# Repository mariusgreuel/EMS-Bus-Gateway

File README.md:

# EMS Bus Gateway

This repository contains a schematic and PCB layout of an **EMS Bus Gateway**. With the EMS Bus Gateway and the [EMS-ESP32](https://github.com/mariusgreuel/EMS-ESP32) firmware, you can connect EMS Bus devices, such as the **Buderus Logamax** boilers to your home automation system.

## Introduction

The assembled EMS Bus Gateway consists of three essential components:

- A voltage level converter that converts the EMS bus voltage levels to 3.3V TTL levels.
- A micro-controller.
- The EMS-ESP32 firmware.

The schematic uses a modified level convertor from the EMS reference schematic circulating the internet. For the micro-controller, a $5 [Seeed Studio XIAO ESP32C3](https://www.seeedstudio.com/Seeed-XIAO-ESP32C3-p-5431.html) board is used. The micro-controller needs to be programmed with [EMS-ESP32](https://github.com/mariusgreuel/EMS-ESP32) firmware, which is capable of decoding the EMS bus protocol and broadcasting the EMS parameters into your network via MQTT. Finally, the assembled board may be fitted into a **Hammond 1551KGY** enclosure.

The assembled EMS Bus Gateway board looks like this:

## EMS Bus Background

Many Buderus devices, such as the **Buderus Logamax plus GB132 T** boiler, use a bus system called **EMS (Energy Management System)** to communicate with other devices, such as the RC30 room controller. The EMS bus is a simple two-wire serial bus that uses voltage/current modulation to transmit data. With the proper hardware and software, you can transmit many parameters of your boiler into your home automation system.

For instance, you could use [Home Assistant](https://www.home-assistant.io/) to monitor the temperatures of your boiler. Here is a screenshot showing the relevant boiler temperatures during a 10 minutes heating interval:

## Build the EMS-ESP32 firmware

To build the EMS-ESP32 firmware, we use the **PlatformIO** toolchain. Please refer to the [PlatformIO documentation](https://docs.platformio.org/en/latest/) on how to install and use **PlatformIO**. According to the original author of the EMS-ESP32 firmware, your should build the firmware on Linux.

Instead of building the firmware locally, you may download pre-built binaries from my [EMS-ESP32 Releases](https://github.com/mariusgreuel/EMS-ESP32/releases).

To setup the **PlatformIO** toolchain, run the following commands in a Linux bash:

```bash
sudo apt install python3
python3 -m venv ~/.venv/ems-esp32
source ~/.venv/ems-esp32/bin/activate
curl -o- https://raw.githubusercontent.com/nvm-sh/nvm/v0.40.1/install.sh | bash
python -m pip install --upgrade pip
pip install platformio
pip install esptool
nvm install 18
nvm use 18
npm install --global yarn
git clone https://github.com/mariusgreuel/ems-esp32.git -b xiao-3.6.5 ~/repos/ems-esp32
```

To build the EMS-ESP32 firmware for a **XIAO ESP32C3**, run the following command:

```bash
source ~/.venv/ems-esp32/bin/activate
nvm use 18
cd ~/repos/ems-esp32
git clean -xdf
platformio run -e seeed_xiao_esp32c3
```

After the build is completed, you will find the binaries in the `.pio\build\seeed_xiao_esp32c3` or `.pio\build\seeed_xiao_esp32s3` folder.

## Flash the EMS-ESP32 firmware

To flash the EMS-ESP32 firmware on the XIAO ESP32, we use the **esptool.py** from Espressif. Please refer to the [Espressif documentation](https://docs.espressif.com/projects/esptool/en/latest/esp32/esptool/index.html) on how to install and use **esptool.py**.

To flash the EMS-ESP32 firmware on a **XIAO ESP32C3**, run the following command:

```bash
esptool.py --chip esp32c3 --port /dev/ttyUSB0 --baud 460800 --before=default_reset --after=hard_reset write_flash 0x0 bootloader.bin 0x8000 partitions.bin 0x10000 firmware.bin
```

## Configure the EMS-ESP32 software

> Note: The documentation below is a quick-start guide to setup the EMS gateway. For detailed instructions, refer to the original documentation at <https://emsesp.github.io/docs/>.

After you have flashed the XIAO ESP32, your need to configure the EMS-ESP32 software to connect it to your local WiFi network. Essentially, the EMS-ESP32 software creates a local WiFi access point that you can connect to. Then, you can open the dashboard of the EMS-ESP32 software using a web browser via a pre-defined username and password and connect the XIAO ESP32 to your local WiFi network:

- Connect the WSP to a USB-C power supply.
- Connect to the new WiFi access point **ems-esp** using the WPA password **ems-esp-neo**.
- Open the URL <http://ems-esp.local/> in a web browser.
- Enter the username **admin** and the password **admin**.

I recommend making the following configuration changes:

- Under **Settings**, set **Board profile** to **Seeed Studio XIAO ESP32C3**.
- Under **Network/Network Settings**, enter the SSID and password of your local WiFi network.
- Under **Access Point/Access Point Settings**, set **Enable Access Point** to **Never**. Before you disable the access point ensure that your EMS Bus gateway has successfully connected to your local WiFi network.
- Under **NTP/NTP Settings**, check **Enable NTP**.
- Under **MQTT/MQTT Settings**, enable MQTT, enter the IP address of your MQTT broker, and enter your MQTT broker credentials. If you run Home Assistant, check **Enable MQTT Discovery**, and set **Discovery Type** to **Home Assistant**.
- Under **Security**, create a new admin user and remove the pre-defined accounts.

As the EMS Bus Gateway is capable of manipulating the settings of your boiler and issuing arbitrary commands, I recommend putting the EMS gateway into **read-only mode**.

> WARNING: If you choose to not enable **read-only mode**, be advised that it is possible to issue powerful commands such starting up the heater of your boiler, which may potentially damage your boiler.

- Under **Settings**, check **Enable read-only mode**.

## Connect the EMS Bus Gateway to your boiler

To connect the EMS Bus Gateway to your boiler, first connect a USB power supply to the USB-C port of the XIAO ESP32. The XIAO ESP32 requires a power supply of 5V. Refer to the [XIAO ESP32C3 documentation](https://wiki.seeedstudio.com/XIAO_ESP32C3_Getting_Started/) for details.

To connect the gateway to the boiler, you can use a 3.5mm TRS audio cable to connect the connector of the EMS Bus Gateway to the service port of your boiler.

The pinout of the TRS service port connector and the EMS Bus Gateway connector is as follows:

Here is a picture of a Buderus Logamax plus GB132T Boiler with a RC30 controller.

Instead of using the service port connector, you can connect a cable directly to the EMS front panel connector of your boiler. In this picture, the left orange/brown connector named **RC** (room controller) may be used. Refer to your boilers service manual for details. The polarity of this connector does not matter.

## Other documents in this repository

- [EMS Bus Gateway Rendering](./docs/ems-bus-gateway-rendering.jpg)
- [EMS Bus Gateway Schematic (PDF))](./docs/ems-bus-gateway-schematic.pdf)
- [EMS Bus Gateway Component Layout (PDF))](./docs/ems-bus-gateway-component-layout.pdf)
- [EMS Bus Gateway Component List (PDF))](./docs/ems-bus-gateway-component-list.pdf)
- [EMS Bus Gateway Gerber Files](./docs/ems-bus-gateway-gerber.zip)
- [EMS Bus Gateway KiCad project](./pcb)

## References

- EMS-ESP Firmware (EMS Bus Gateway Fork): <https://github.com/mariusgreuel/EMS-ESP32>
- EMS-ESP Firmware (Original): <https://github.com/emsesp/EMS-ESP32>
- EMS-ESP Firmware Documentation: <https://emsesp.github.io/docs/>
- Seeed Studio XIAO Documentation: <https://wiki.seeedstudio.com/SeeedStudio_XIAO_Series_Introduction/>

## License

The EMS Bus Gateway schematic, PCB layout, and documentation is released under the GNU GPLv3.

Copyright 2023 Marius Greuel.

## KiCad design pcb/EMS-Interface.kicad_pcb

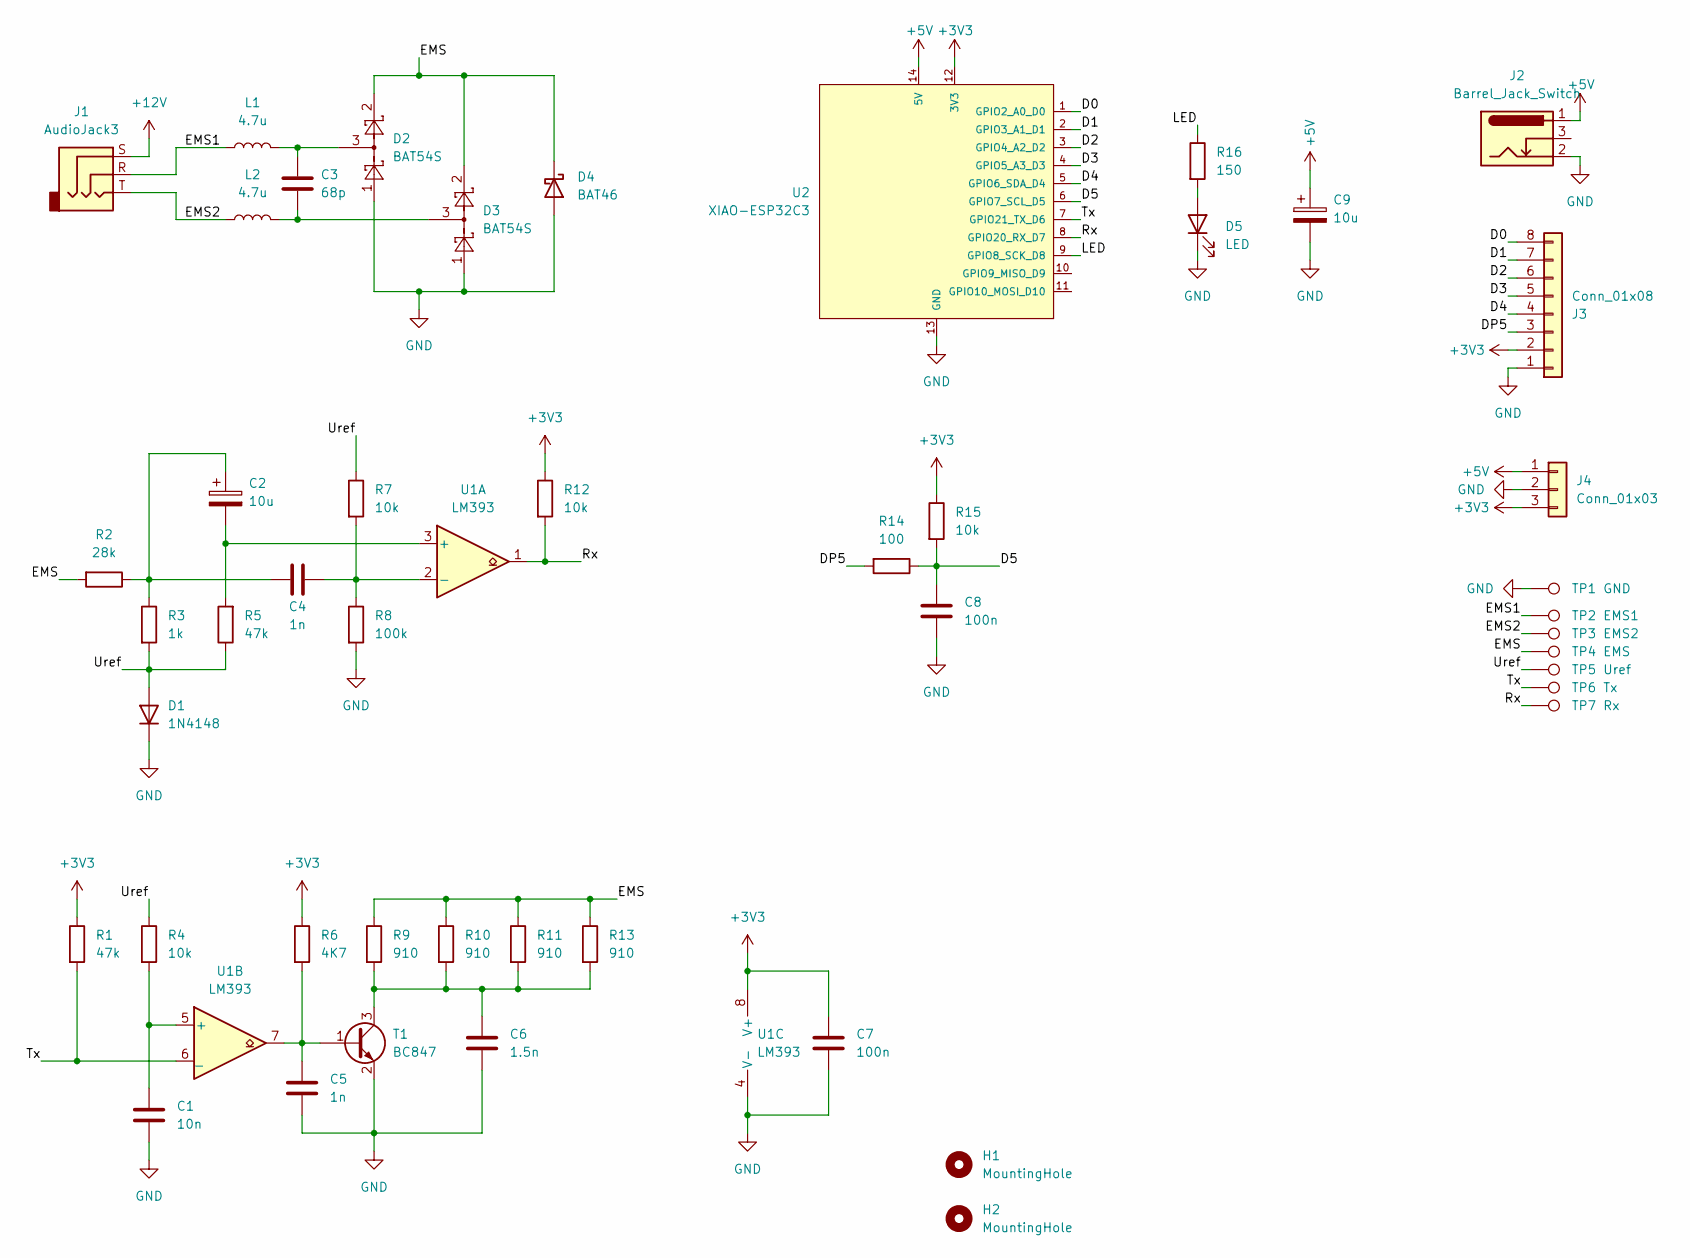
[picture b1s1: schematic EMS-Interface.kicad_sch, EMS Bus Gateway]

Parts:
C1: 10n; C_0805_2012Metric
C2, C9: 10u; CP_EIA-6032-28_Kemet-C
C3: 68p; C_0805_2012Metric
C4, C5: 1n; C_0805_2012Metric
C6: 1.5n; C_0805_2012Metric
C7, C8: 100n; C_0805_2012Metric
D1: 1N4148; D_SOD-123
D2, D3: BAT54S; SOT-23
D4: BAT46; D_SOD-123
D5: LED; LED_0805_2012Metric
H1, H2: MountingHole; MountingHole_2.5mm
J1: AudioJack3; Jack_3.5mm_Lumberg_1503_07_Horizontal
J2: Barrel_Jack_Switch; Lumberg-NEB-21-R
J3: Conn_01x08; PinHeader_1x08_P2.54mm_Vertical
J4: Conn_01x03; PinHeader_1x03_P2.54mm_Vertical
L1, L2: 4.7u; L_1210_3225Metric
R1, R5: 47k; R_0805_2012Metric
R2: 28k; R_0805_2012Metric
R3: 1k; R_0805_2012Metric
R4, R7, R12, R15: 10k; R_0805_2012Metric
R6: 4K7; R_0805_2012Metric
R8: 100k; R_0805_2012Metric
R9, R10, R11, R13: 910; R_0805_2012Metric
R14: 100; R_0805_2012Metric
R16: 150; R_0805_2012Metric
T1: BC847; SOT-23
TP1: GND; TestPoint_Pad_D1.0mm
TP2: EMS1; TestPoint_Pad_D1.0mm
TP3: EMS2; TestPoint_Pad_D1.0mm
TP4: EMS; TestPoint_Pad_D1.0mm
TP5: Uref; TestPoint_Pad_D1.0mm
TP6: Tx; TestPoint_Pad_D1.0mm
TP7: Rx; TestPoint_Pad_D1.0mm
U1: LM393; SO-8_3.9x4.9mm_P1.27mm
U2: XIAO-ESP32C3; Seeed Studio XIAO

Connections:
+3V3: C7.1, J3.2, J4.3, R1.1, R6.1, R12.1, R15.1, U1.8 (V+), U2.12 (3V3)
+5V: C9.1, J2.1, J4.1, U2.14 (5V)
+12V: J1.S
/D0: J3.8, U2.1 (GPIO2_A0_D0)
/D1: J3.7, U2.2 (GPIO3_A1_D1)
/D2: J3.6, U2.3 (GPIO4_A2_D2)
/D3: J3.5, U2.4 (GPIO5_A3_D3)
/D4: J3.4, U2.5 (GPIO6_SDA_D4)
/D5: C8.1, R14.1, R15.2, U2.6 (GPIO7_SCL_D5)
/DP5: J3.3, R14.2
/EMS: D2.2, D3.2, D4.1 (K), R2.2, R9.1, R10.1, R11.1, R13.1, TP4.1
/EMS1: J1.R, L1.1, TP2.1
/EMS2: J1.T, L2.1, TP3.1
/LED: R16.1, U2.9 (GPIO8_SCK_D8)
/Rx: R12.2, TP7.1, U1.1, U2.8 (GPIO20_RX_D7)
/Tx: R1.2, TP6.1, U1.6 (_), U2.7 (GPIO21_TX_D6)
/Uref: D1.2 (A), R3.2, R4.1, R5.1, R7.1, TP5.1
GND: C1.2, C5.2, C6.2, C7.2, C8.2, C9.2, D1.1 (K), D2.1, D3.1, D4.2 (A), D5.1 (K), J2.2, J3.1, J4.2, R8.2, T1.2 (E), TP1.1, U1.4 (V-), U2.13 (GND)
unnamed: C2.1, C4.2, R2.1, R3.1
unnamed: C3.1, D2.3, L1.2
unnamed: C3.2, D3.3, L2.2
unnamed: D5.2 (A), R16.2
unnamed: C5.1, R6.2, T1.1 (B), U1.7
unnamed: C6.1, R9.2, R10.2, R11.2, R13.2, T1.3 (C)
unnamed: C2.2, R5.2, U1.3 (+)
unnamed: C4.1, R7.2, R8.1, U1.2 (-)
unnamed: C1.1, R4.2, U1.5 (+)

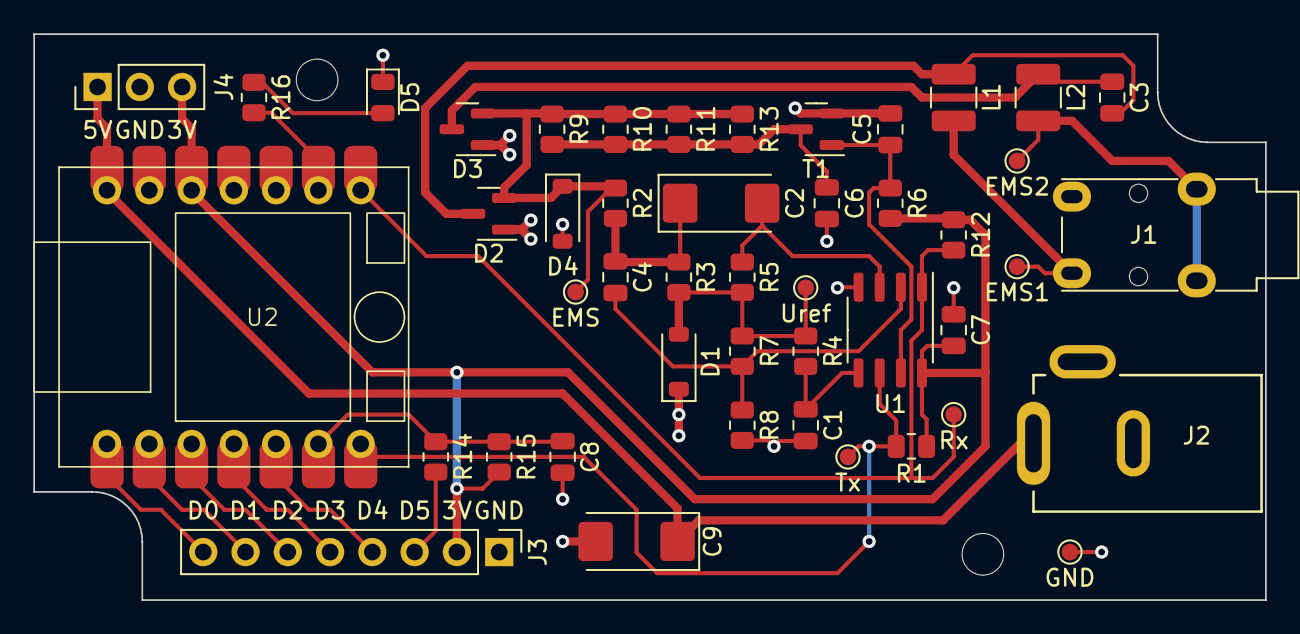
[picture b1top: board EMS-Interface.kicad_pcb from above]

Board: 2 copper layers, 74.0 x 34.0 mm, 48 parts (0 on the bottom side), 26 nets.

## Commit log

2023-10-03 Update documentation
2024-06-22 add: component placement chart for manual placement
2024-10-03 Update README.md for v3.6.5 release

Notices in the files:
pcb/EMS-Interface.kicad_pcb:
© 2023 Marius Greuel
